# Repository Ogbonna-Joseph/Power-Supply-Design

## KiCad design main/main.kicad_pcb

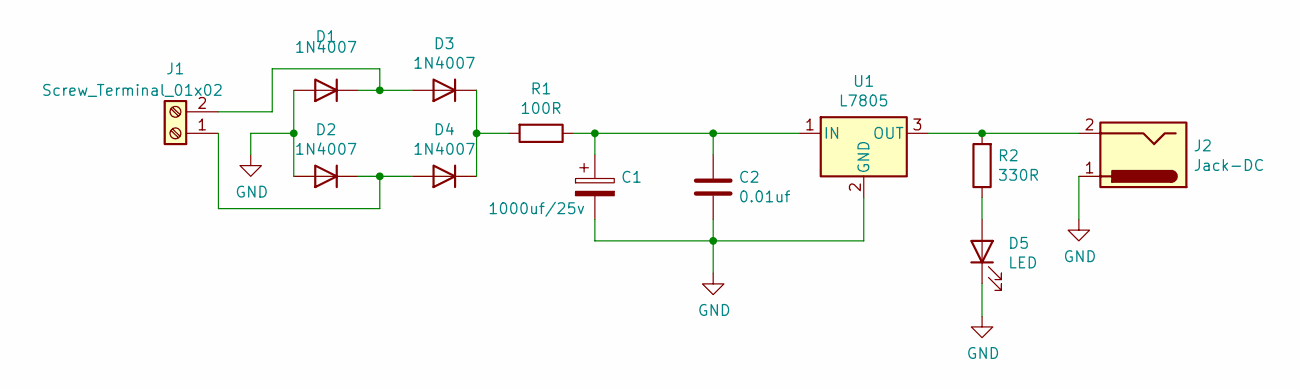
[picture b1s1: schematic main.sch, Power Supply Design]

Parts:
C1: 1000uf/25v; CP_Radial_D12.5mm_P7.50mm
C2: 0.01uf; C_Disc_D8.0mm_W5.0mm_P5.00mm
D1, D2, D3, D4: 1N4007; D_DO-15_P15.24mm_Horizontal
D5: LED; LED_D8.0mm
J1: Screw_Terminal_01x02; TerminalBlock_Phoenix_MKDS-3-2-5.08_1x02_P5.08mm_Horizontal
J2: Jack-DC; TerminalBlock_bornier-2_P5.08mm
R1: 100R; R_Axial_DIN0204_L3.6mm_D1.6mm_P7.62mm_Horizontal
R2: 330R; R_Axial_DIN0204_L3.6mm_D1.6mm_P7.62mm_Horizontal
U1: L7805; TO-220-3_Vertical

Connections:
GND: C1.2, C2.2, D1.2 (A), D2.2 (A), D5.1 (K), J2.1, U1.2 (GND)
unnamed: C1.1, C2.1, R1.1, U1.1 (IN)
unnamed: D1.1 (K), D3.2 (A), J1.2
unnamed: D2.1 (K), D4.2 (A), J1.1
unnamed: D3.1 (K), D4.1 (K), R1.2
unnamed: D5.2 (A), R2.1
unnamed: J2.2, R2.2, U1.3 (OUT)

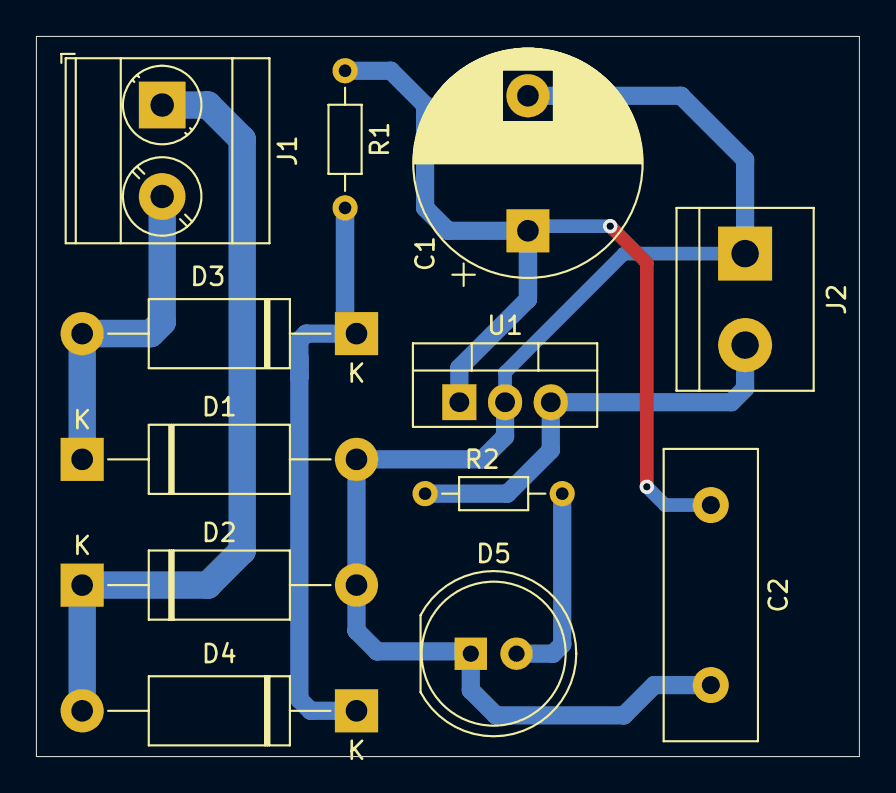
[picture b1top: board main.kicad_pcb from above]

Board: 2 copper layers, 45.7 x 40.0 mm, 12 parts (0 on the bottom side), 7 nets.
